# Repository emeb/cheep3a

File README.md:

# cheep3a
An inexpensive Eurorack audio generator

## Abstract
This project is an extension of previous "Cheep" Eurorack modules which have been
built as demonstrations for simple, low-cost audio generators using low-end MCUs
and DACs. Cheep3a targets the recently introduced CH32V003 RISC-V based MCU from
WCH Inc. in order to explore the feasibility of audio generation with a sub-$1.00
microcontroller.

## Features
Cheep3a provides the following features:
* Three Control Voltage inputs with 10-bit 10Vpp instantaneous range over a +/-11V
adjustable range using offset potentiometers.
* One digital input for trigger/gate/sync.
* Two +/-5V audio outputs with 16-bit resolution and 48kHz sample rate.
* One mode select button
* One RGB LED for mode indication.
* 4-pin programming interface, including 1-line WCH standard SWDIO, UART TX and
Reset signal.
* JST SH-4 connector with optional I2C signals compatible with StemmaQT/Qwiic
connections for off-board expansion.
* Standard 16-pin Eurorack power with shrouded header and +/-12V supply.

## Firmware
Firmware included in this project supports seven operating modes with various
audio signal outputs in each mode:
1. [Red] Two independent sine oscillators with amplitude control - 10Hz - 10kHz
frequency range.
2. [Green] Same as 1 but with 0.3Hz - 300Hz frequency range.
3. [Yellow] One sine oscillator with two outputs, phase offset and amplitude
control - 10Hz - 10kHz frequency range.
4. [Blue] Pulse wave oscillator with two outputs and independent PWM
controls - 10Hz - 10kHz frequency range.
5. [Magenta] 2-operator FM with index and ratio controls. Mod and Carrier outputs.
6. [Cyan] Two independent clocked noise outputs.
7. [White] White and Pink noise outputs.

Mode selection is stored in the MCU's on-chip flash memory and will persist
across power cycles.

### Building Firmware
The Cheep3a firmware is based on [cnlohr's "ch32v003fun"](https://github.com/cnlohr/ch32v003fun)
project and expects that the github directory for that project is located in
an adjacent directory in order for the make-based build system to operate
correctly. A recent RISC-V GCC toolchain is also required and once you have
that installed (and in your search path) the following steps should work:

```
git clone git@github.com:emeb/cheep3a.git
git clone git@github.com:cnlohr/ch32v003fun.git
cd cheep3a/firmware
make
```

## Hardware
Version 0.1 of the hardware was fabbed and assembled at JLCPCB at modest cost and
all unsupported components (pots, jacks, connectors, LED and button) were added
by hand. Aside from a few minor layout errors which were easily corrected, the
system performed as expected.

### Building Hardware
The hardware can be recreated with the following steps:
1. Open the PCB project in Kicad and generate Gerber and Drill files. Zip them
up together and submit to the PCB fab of choice.
2. Generate component placement information and format as required by your
PCB assembly house.
3. The JLCPCB formatted BOM is included in the hardware directory and maps to
components that were available at the time I designed this board. If you don't
use JLCPCB the BOM may need to be reformatted and substitutions of parts will
likely be necessary.
4. Follow the submission process for your PCB house, including correction of
placement and approval of components.

## Lessons Learned
The CH32V003 MCU performs well for simple audio generation tasks but falls
somewhat short for more complex DSP. Hardware support for good digital audio is
impaired by the overall low CPU clock speed and limited memory capcity, as well
as the need to "work around" the lack of true I2S serial audio interfacing. The
biggest shortcoming however is the subset RV32E RISC-V CPU which doesn't provide
hardware multiply and thus significantly increases the cost of even simple DSP
operations needed for good-quality audio generation.

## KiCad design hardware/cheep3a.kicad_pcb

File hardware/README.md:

# Hardware
This directory contains the KiCad project files for the Cheep3a hardware design.

# Version
This is Version 0.2

* Version 0.1 of the design was fabbed and assembled by JLCPCB and several minor
issues were discovered. These issues were corrected and the system performed as
designed.
* Version 0.2 corrects the errors found in V0.1 but has not been built or tested.

# Panel Design
The directory `cheep3a_panel` contains a front panel design for standard 3U
Eurorack mounting.

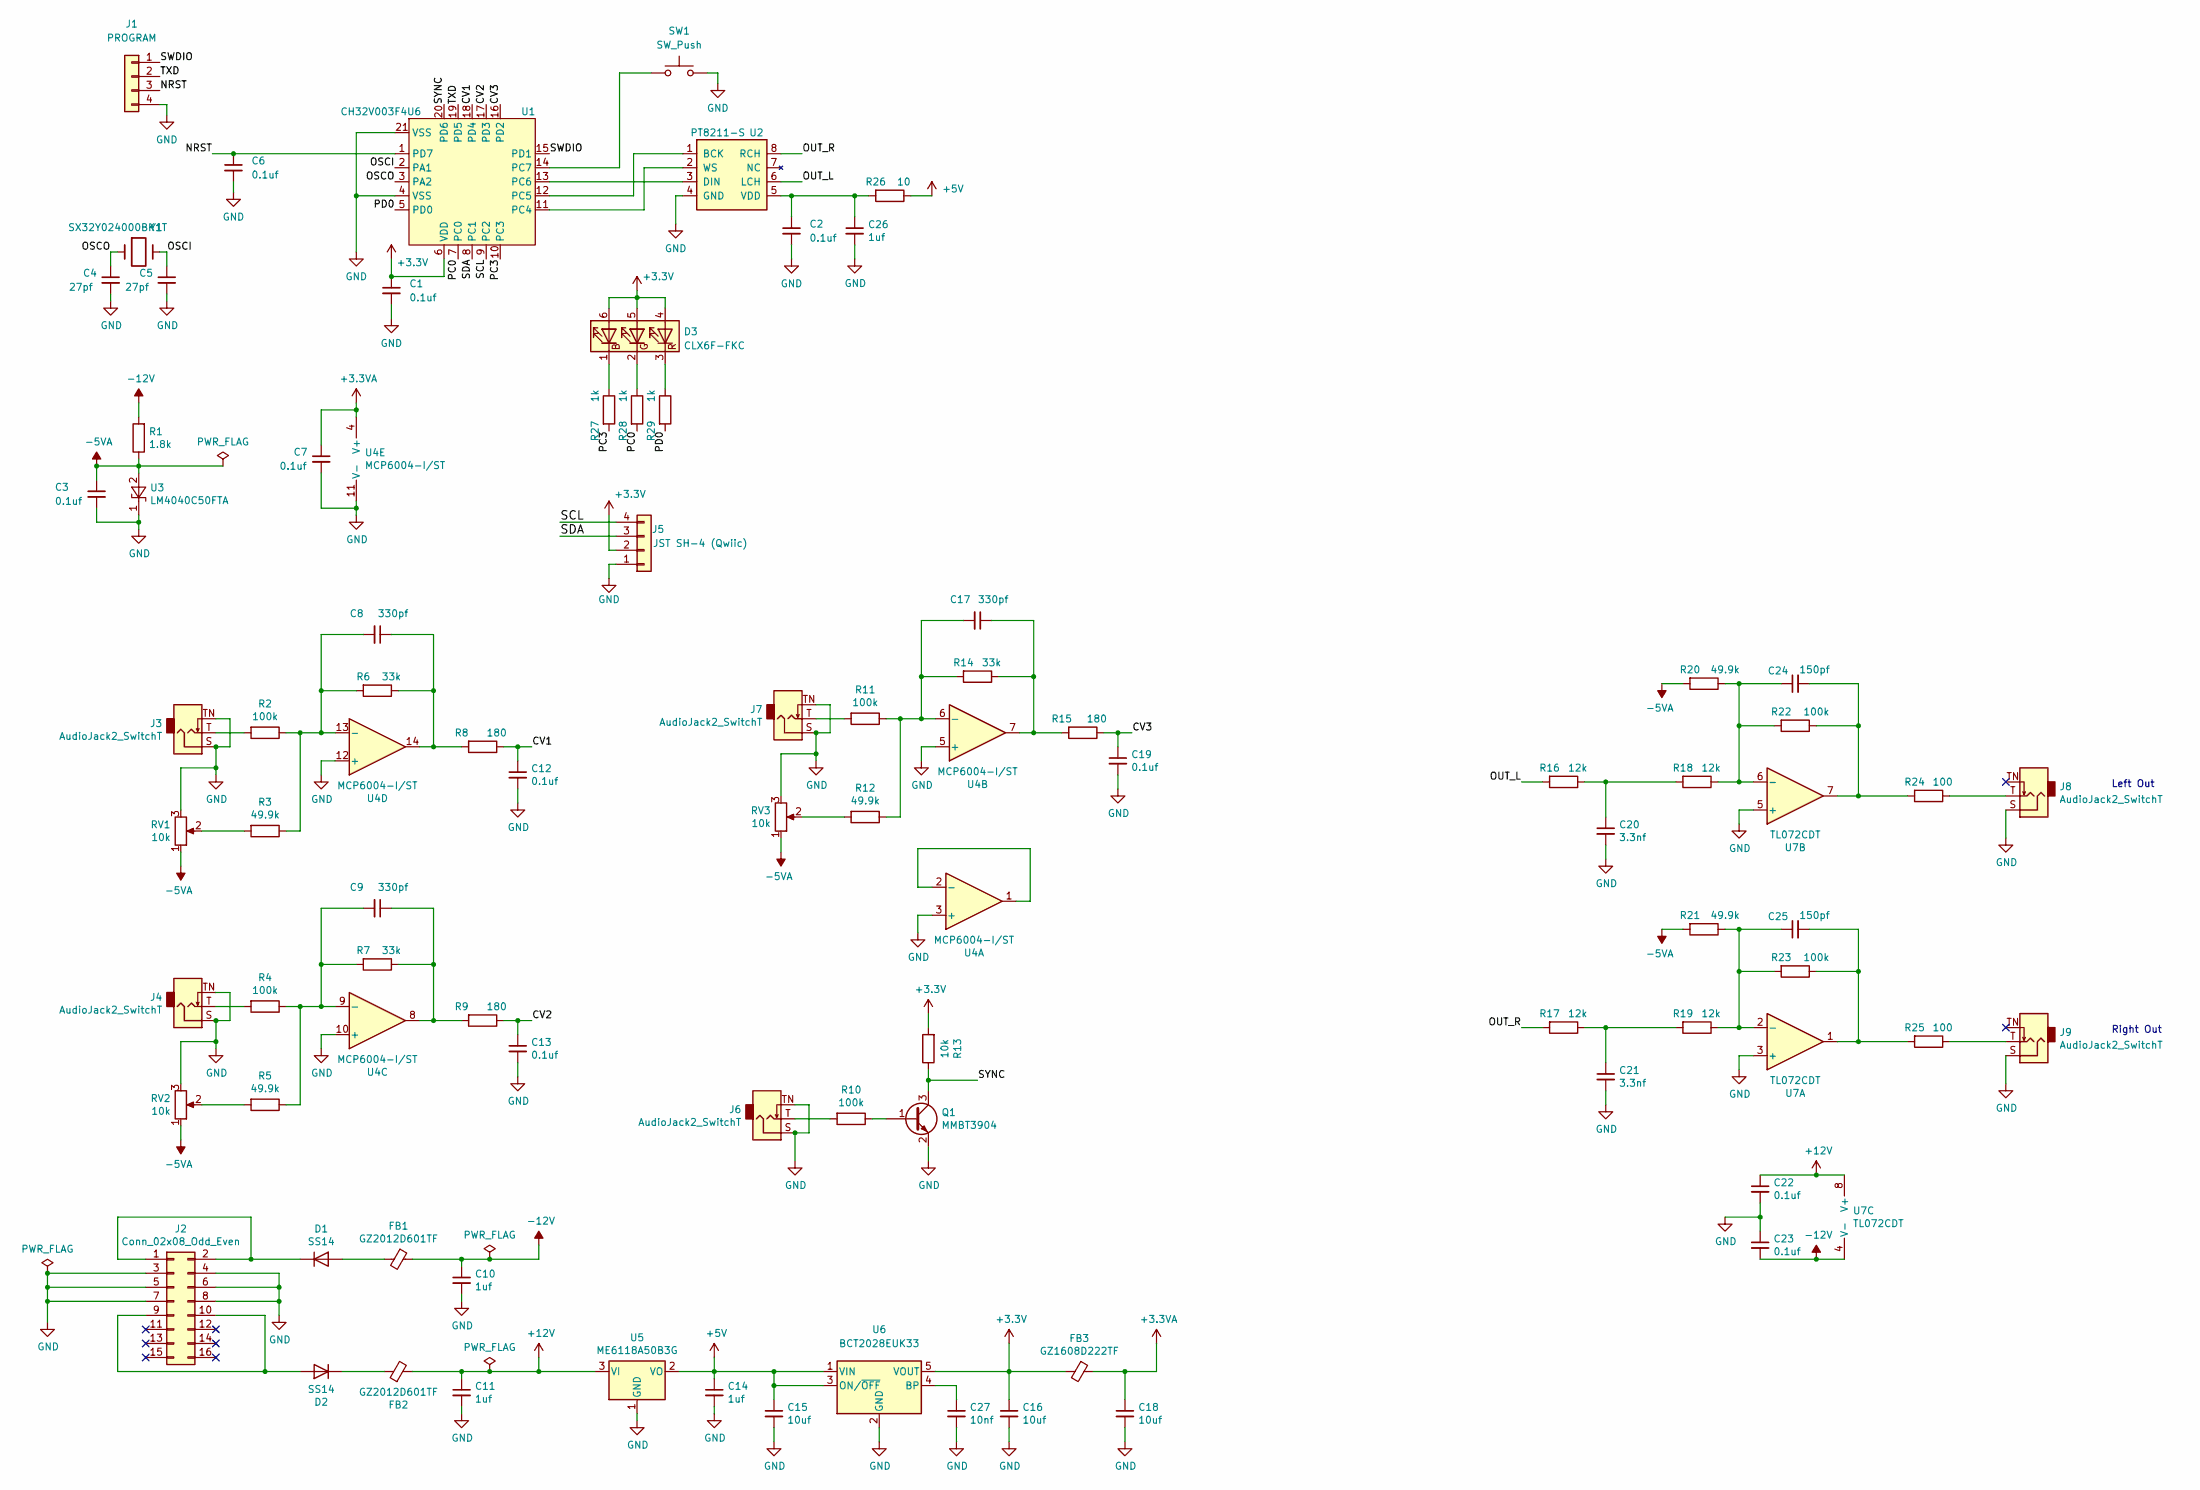
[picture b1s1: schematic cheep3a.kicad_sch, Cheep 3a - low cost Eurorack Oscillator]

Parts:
C1, C2, C3, C6, C7, C12, C13, C19, C22, C23: 0.1uf; C_0603_1608Metric
C4, C5: 27pf; C_0603_1608Metric
C8, C9, C17: 330pf; C_0603_1608Metric
C10, C11, C14, C26: 1uf; C_0603_1608Metric
C15, C16, C18: 10uf; C_0805_2012Metric
C20, C21: 3.3nf; C_0603_1608Metric
C24, C25: 150pf; C_0603_1608Metric
C27: 10nf; C_0603_1608Metric
D1, D2: SS14; D_SMA
D3: CLX6F-FKC; LED_RGB_PLCC-6
FB1, FB2: GZ2012D601TF; L_0805_2012Metric
FB3: GZ1608D222TF; L_0603_1608Metric
J1: PROGRAM; PinHeader_1x04_P2.54mm_Vertical
J2: Conn_02x08_Odd_Even; con16_2X8_S4_TEC
J3, J4, J6, J7, J8, J9: AudioJack2_SwitchT; Jack_3.5mm_QingPu_WQP-PJ398SM_Vertical_CircularHoles
J5: JST SH-4 (Qwiic); JST_SH_SM04B-SRSS-TB_04x1.00mm_Angled
Q1: MMBT3904; SOT-23
R1: 1.8k; R_0603_1608Metric
R2, R4, R10, R11, R22, R23: 100k; R_0603_1608Metric
R3, R5, R12, R20, R21: 49.9k; R_0603_1608Metric
R6, R7, R14: 33k; R_0603_1608Metric
R8, R9, R15: 180; R_0603_1608Metric
R13: 10k; R_0603_1608Metric
R16, R17, R18, R19: 12k; R_0603_1608Metric
R24, R25: 100; R_0603_1608Metric
R26: 10; R_0603_1608Metric
R27, R28, R29: 1k; R_0603_1608Metric
RV1, RV2, RV3: 10k; Potentiometer_TT_P0915N
SW1: SW_Push; SW_PUSH_6mm
U1: CH32V003F4U6; QFN-20-1EP_3x3mm_P0.4mm_EP1.65x1.65mm_ThermalVias
U2: PT8211-S; SO-8_3.9x4.9mm_P1.27mm
U3: LM4040C50FTA; SOT-23
U4: MCP6004-I/ST; TSSOP-14_4.4x5mm_P0.65mm
U5: ME6118A50B3G; SOT-223-3_TabPin2
U6: BCT2028EUK33; SOT-23-5
U7: TL072CDT; SOIC-8_3.9x4.9mm_P1.27mm
Y1: SX32Y024000BK1T; Crystal_SMD_3225-4Pin_3.2x2.5mm

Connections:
+3.3V: C1.1, C16.1, D3.4 (BA), D3.5 (GA), D3.6 (RA), FB3.2, J5.2, R13.2, U1.6 (VDD), U6.5 (VOUT)
+3.3VA: C7.1, C18.1, FB3.1, U4.4 (V+)
+5V: C14.1, C15.1, R26.1, U5.2 (VO), U6.1 (VIN), U6.3 (ON/~OFF)
+12V: C11.1, C22.1, FB2.2, U5.3 (VI), U7.8 (V+)
-5VA: C3.1, R1.1, R20.2, R21.2, RV1.1, RV2.1, RV3.1, U3.2 (A)
-12V: C10.1, C23.2, FB1.1, R1.2, U7.4 (V-)
/CV1: C12.1, R8.1, U1.18 (PD4)
/CV2: C13.1, R9.1, U1.17 (PD3)
/CV3: C19.1, R15.1, U1.16 (PD2)
/NRST: C6.1, J1.3, U1.1 (PD7)
/OSCI: C5.1, U1.2 (PA1), Y1.3
/OSCO: C4.1, U1.3 (PA2), Y1.1
/OUT_L: R16.2, U2.6 (LCH)
/OUT_R: R17.2, U2.8 (RCH)
/PC0: R28.2, U1.7 (PC0)
/PC3: R27.2, U1.10 (PC3)
/PD0: R29.2, U1.5 (PD0)
/SCL: J5.4, U1.9 (PC2)
/SDA: J5.3, U1.8 (PC1)
/SWDIO: J1.1, U1.15 (PD1)
/SYNC: Q1.3 (C), R13.1, U1.20 (PD6)
/TXD: J1.2, U1.19 (PD5)
GND: C1.2, C2.2, C3.2, C4.2, C5.2, C6.2, C7.2, C10.2, C11.2, C12.2, C13.2, C14.2, C15.2, C16.2, C18.2, C19.2, C20.2, C21.2, C22.2, C23.1, C26.2, C27.2, J1.4, J2.3, J2.4, J2.5, J2.6, J2.7, J2.8, J3.S, J3.TN, J4.S, J4.TN, J5.1, J6.S, J6.TN, J7.S, J7.TN, J8.S, J9.S, Q1.2 (E), RV1.3, RV2.3, RV3.3, SW1.2, U1.4 (VSS), U1.21 (VSS), U2.4 (GND), U3.1 (K), U4.3 (+), U4.5 (+), U4.10 (+), U4.11 (V-), U4.12 (+), U5.1 (GND), U6.2 (GND), U7.3 (+), U7.5 (+)
unnamed: C2.1, C26.1, R26.2, U2.5 (VDD)
unnamed: C8.1, R6.1, R8.2, U4.14
unnamed: C8.2, R2.1, R3.1, R6.2, U4.13 (-)
unnamed: C9.1, R7.1, R9.2, U4.8
unnamed: C9.2, R4.1, R5.1, R7.2, U4.9 (-)
unnamed: C17.1, R14.1, R15.2, U4.7
unnamed: C17.2, R11.1, R12.1, R14.2, U4.6 (-)
unnamed: C20.1, R16.1, R18.2
unnamed: C21.1, R17.1, R19.2
unnamed: C24.1, R18.1, R20.1, R22.2, U7.6 (-)
unnamed: C24.2, R22.1, R24.2, U7.7
unnamed: C25.1, R19.1, R21.1, R23.2, U7.2 (-)
unnamed: C25.2, R23.1, R25.2, U7.1
unnamed: C27.1, U6.4 (BP)
unnamed: D1.1 (K), J2.1, J2.2
unnamed: D1.2 (A), FB1.2
unnamed: D2.1 (K), FB2.1
unnamed: D2.2 (A), J2.9, J2.10
unnamed: D3.1 (RK), R27.1
unnamed: D3.2 (GK), R28.1
unnamed: D3.3 (BK), R29.1
unnamed: J3.T, R2.2
unnamed: J4.T, R4.2
unnamed: J6.T, R10.2
unnamed: J7.T, R11.2
unnamed: J8.T, R24.1
unnamed: J9.T, R25.1
unnamed: Q1.1 (B), R10.1
unnamed: R3.2, RV1.2
unnamed: R5.2, RV2.2
unnamed: R12.2, RV3.2
unnamed: SW1.1, U1.14 (PC7)
unnamed: U1.11 (PC4), U2.2 (WS)
unnamed: U1.12 (PC5), U2.1 (BCK)
unnamed: U1.13 (PC6), U2.3 (DIN)
unnamed: U4.1, U4.2 (-)

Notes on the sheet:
Right Out
Left Out

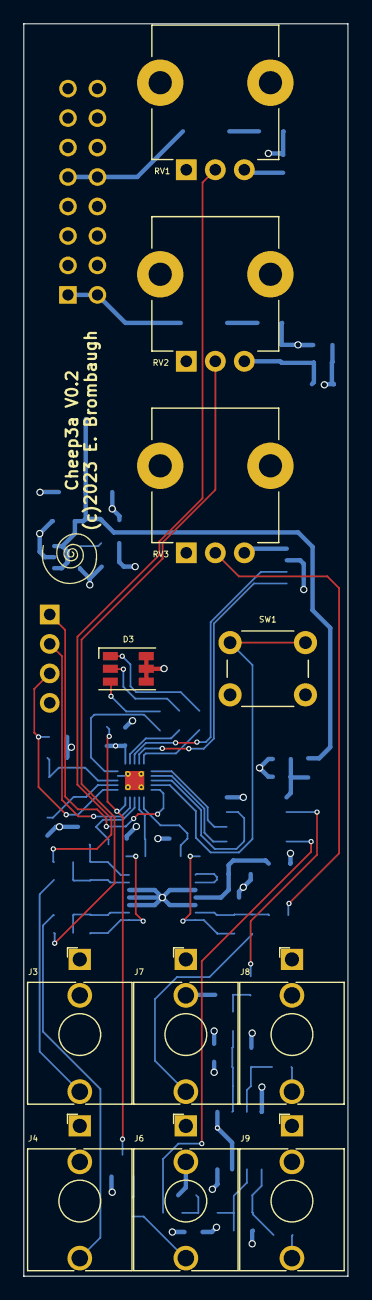
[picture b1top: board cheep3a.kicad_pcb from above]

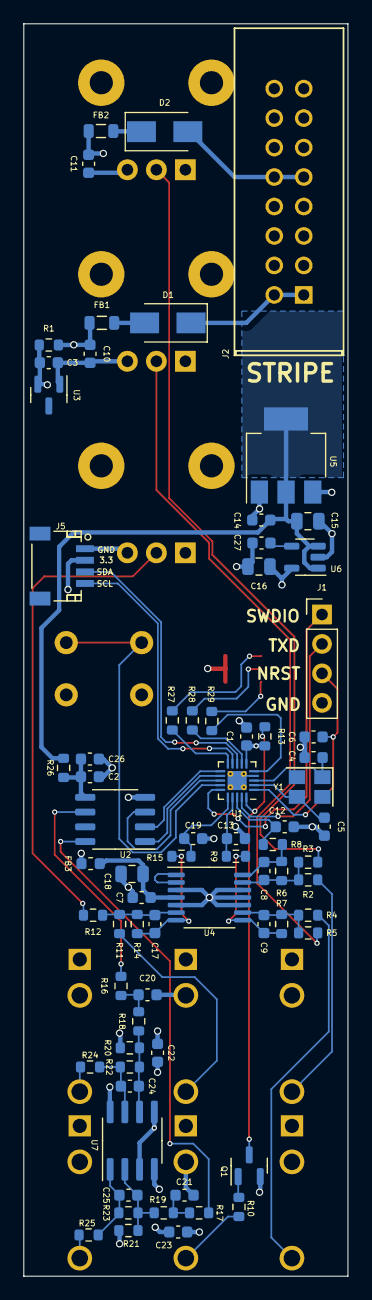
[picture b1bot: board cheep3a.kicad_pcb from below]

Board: 4 copper layers, 27.9 x 108.0 mm, 85 parts (73 on the bottom side), 59 nets.

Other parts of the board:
Ref**: Val**; avatar_small

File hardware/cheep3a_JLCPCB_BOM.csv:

Comment,Designator,Footprint,JLCPCB Part#
0.1uf,"C1, C2, C3, C6, C7, C12, C13, C19, C22, C23",Capacitor_SMD:C_0603_1608Metric,C14663
27pf,"C4, C5",Capacitor_SMD:C_0603_1608Metric,C107045
330pf,"C8, C9, C17",Capacitor_SMD:C_0603_1608Metric,C1664
1uf,"C10, C11, C14, C26",Capacitor_SMD:C_0603_1608Metric,C15849
10uf,"C15, C16, C18",Capacitor_SMD:C_0805_2012Metric,C440198
3.3nf,"C20, C21",Capacitor_SMD:C_0603_1608Metric,C1613
150pf,"C24, C25",Capacitor_SMD:C_0603_1608Metric,C1594
10nf,C27,Capacitor_SMD:C_0603_1608Metric,C57112
SS14,"D1, D2",Diode_SMD:D_SMA,C2480
GZ2012D601TF,"FB1, FB2",Inductor_SMD:L_0805_2012Metric,C1017
GZ1608D222TF,FB3,Inductor_SMD:L_0603_1608Metric,C96697
1.8k,R1,Resistor_SMD:R_0603_1608Metric,C4177
100k,"R2, R4, R10, R11, R22, R23",Resistor_SMD:R_0603_1608Metric,C25803
49.9k,"R3, R5, R12, R20, R21",Resistor_SMD:R_0603_1608Metric,C23184
33k,"R6, R7, R14",Resistor_SMD:R_0603_1608Metric,C4216
180,"R8, R9, R15",Resistor_SMD:R_0603_1608Metric,C22828
10k,R13,Resistor_SMD:R_0603_1608Metric,C25804
12k,"R16, R17, R18, R19",Resistor_SMD:R_0603_1608Metric,C22790
100,"R24, R25",Resistor_SMD:R_0603_1608Metric,C22775
10,R26,Resistor_SMD:R_0603_1608Metric,C22859
1k,"R27, R28, R29",Resistor_SMD:R_0603_1608Metric,C21190
CH32V003F4U6,U1,Package_DFN_QFN:QFN-20-1EP_3x3mm_P0.4mm_EP1.65x1.65mm_ThermalVias,C5299908
PT8211-S,U2,Package_SO:SO-8_3.9x4.9mm_P1.27mm,C92004
LM4040C50FTA,U3,Package_TO_SOT_SMD:SOT-23,C156291
MCP6004-I/ST,U4,Package_SO:TSSOP-14_4.4x5mm_P0.65mm,C50282
ME6118A50B3G,U5,Package_TO_SOT_SMD:SOT-223-3_TabPin2,C151064
BCT2028EUK33,U6,Package_TO_SOT_SMD:SOT-23-5,C266766
TL072CDT,U7,Package_SO:SOIC-8_3.9x4.9mm_P1.27mm,C6961
SX32Y024000BK1T,Y1,Crystal:Crystal_SMD_3225-4Pin_3.2x2.5mm,C271630
MMBT3904,Q1,Package_TO_SOT_SMD:SOT-23,C909754

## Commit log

2023-07-25 Initial checkin
2023-07-25 fix image link
2023-07-25 Add link
2023-07-27 Improved sine phase resolution 16x, added 2-op FM mode, clean up PWM ends.

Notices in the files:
hardware/cheep3a.kicad_pcb:
(c)2023 E. Brombaugh
